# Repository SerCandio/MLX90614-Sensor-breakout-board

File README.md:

# MLX90614-Sensor-breakout-board
This is a pretty small breakout-board for MLX90614 infra-red thermometer

# LAYOUTS
Podemos ver una version terminada de la tarjeta PCB a continuacion(elaborado en EAGLE - Fusion 360):

# GERBER
Desde este link:  podemos descargar los archivos de fabricacion: https://github.com/SerCandio/MLX90614-Sensor-breakout-board/tree/main/GERBER

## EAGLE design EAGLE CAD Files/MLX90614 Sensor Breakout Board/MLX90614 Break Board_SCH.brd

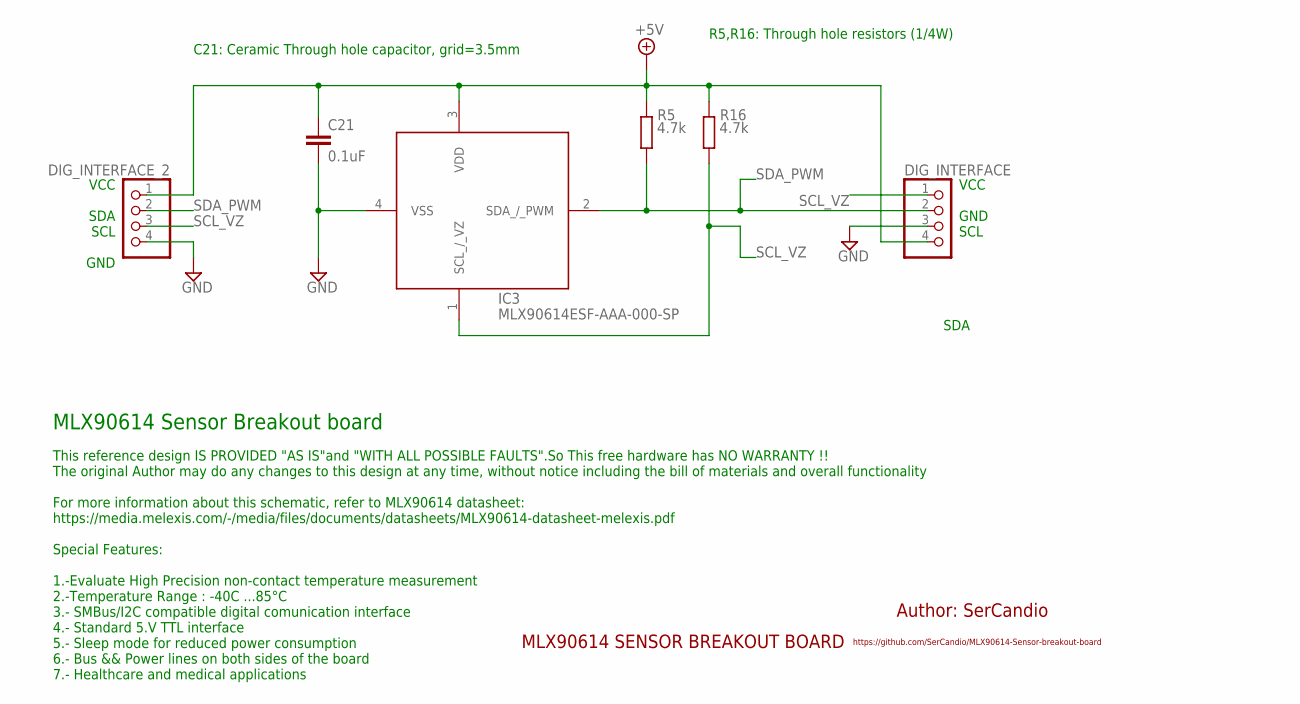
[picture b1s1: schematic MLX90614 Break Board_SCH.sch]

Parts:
C21: 0.1uF; C025-025X050
DIG_INTERFACE: PINHD-1X4/90; 1X04/90
DIG_INTERFACE_2: PINHD-1X4/90; 1X04/90
IC3: MLX90614ESF-AAA-000-SP; MLX90614ESFAAA000SP
R5, R16: 4.7k; 0207/10

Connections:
+5V: C21.1, DIG_INTERFACE.4, DIG_INTERFACE_2.1, IC3.3 (VDD), R5.1, R16.1
GND: C21.2, DIG_INTERFACE.3, DIG_INTERFACE_2.4, IC3.4 (VSS)
SCL_VZ: DIG_INTERFACE.1, DIG_INTERFACE_2.3, IC3.1 (SCL_/_VZ), R16.2
SDA_PWM: DIG_INTERFACE.2, DIG_INTERFACE_2.2, IC3.2 (SDA_/_PWM), R5.2

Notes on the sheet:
MLX90614 Sensor Breakout board
This reference design IS PROVIDED "AS IS"and "WITH ALL POSSIBLE FAULTS".So This free hardware has NO WARRANTY !!
The original Author may do any changes to this design at any time, without notice including the bill of materials and overall functionality
For more information about this schematic, refer to MLX90614 datasheet:
https://media.melexis.com/-/media/files/documents/datasheets/MLX90614-datasheet-melexis.pdf
Special Features:
1.-Evaluate High Precision non-contact temperature measurement
2.-Temperature Range : -40C ...85°C
3.- SMBus/I2C compatible digital comunication interface
4.- Standard 5.V TTL interface
5.- Sleep mode for reduced power consumption
6.- Bus && Power lines on both sides of the board
7.- Healthcare and medical applications
SDA
SCL
GND
VCC
R5,R16: Through hole resistors (1/4W)
C21: Ceramic Through hole capacitor, grid=3.5mm
MLX90614 SENSOR BREAKOUT BOARD
Author: SerCandio
https://github.com/SerCandio/MLX90614-Sensor-breakout-board

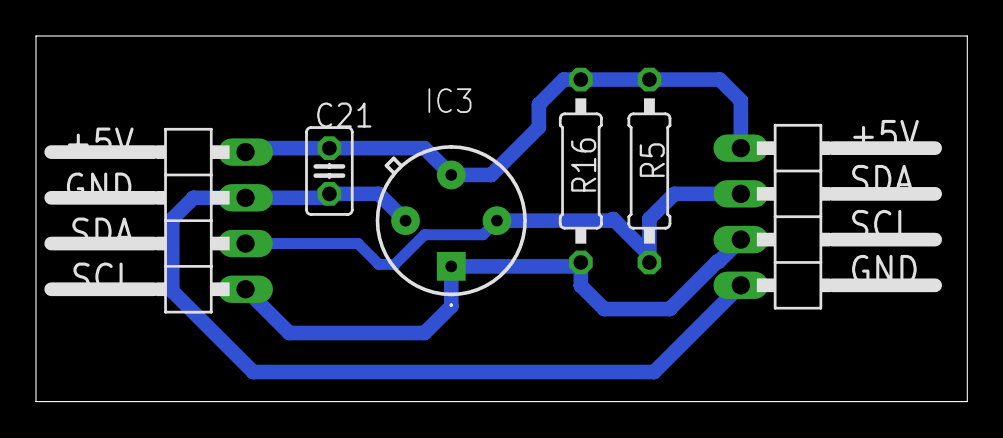
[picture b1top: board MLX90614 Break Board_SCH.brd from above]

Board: 2 copper layers, 51.7 x 20.3 mm, 6 parts (0 on the bottom side), 4 nets.

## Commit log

2024-03-04 Eagle CAD Files
2024-03-04 EAGLE Schematic Diagrams
